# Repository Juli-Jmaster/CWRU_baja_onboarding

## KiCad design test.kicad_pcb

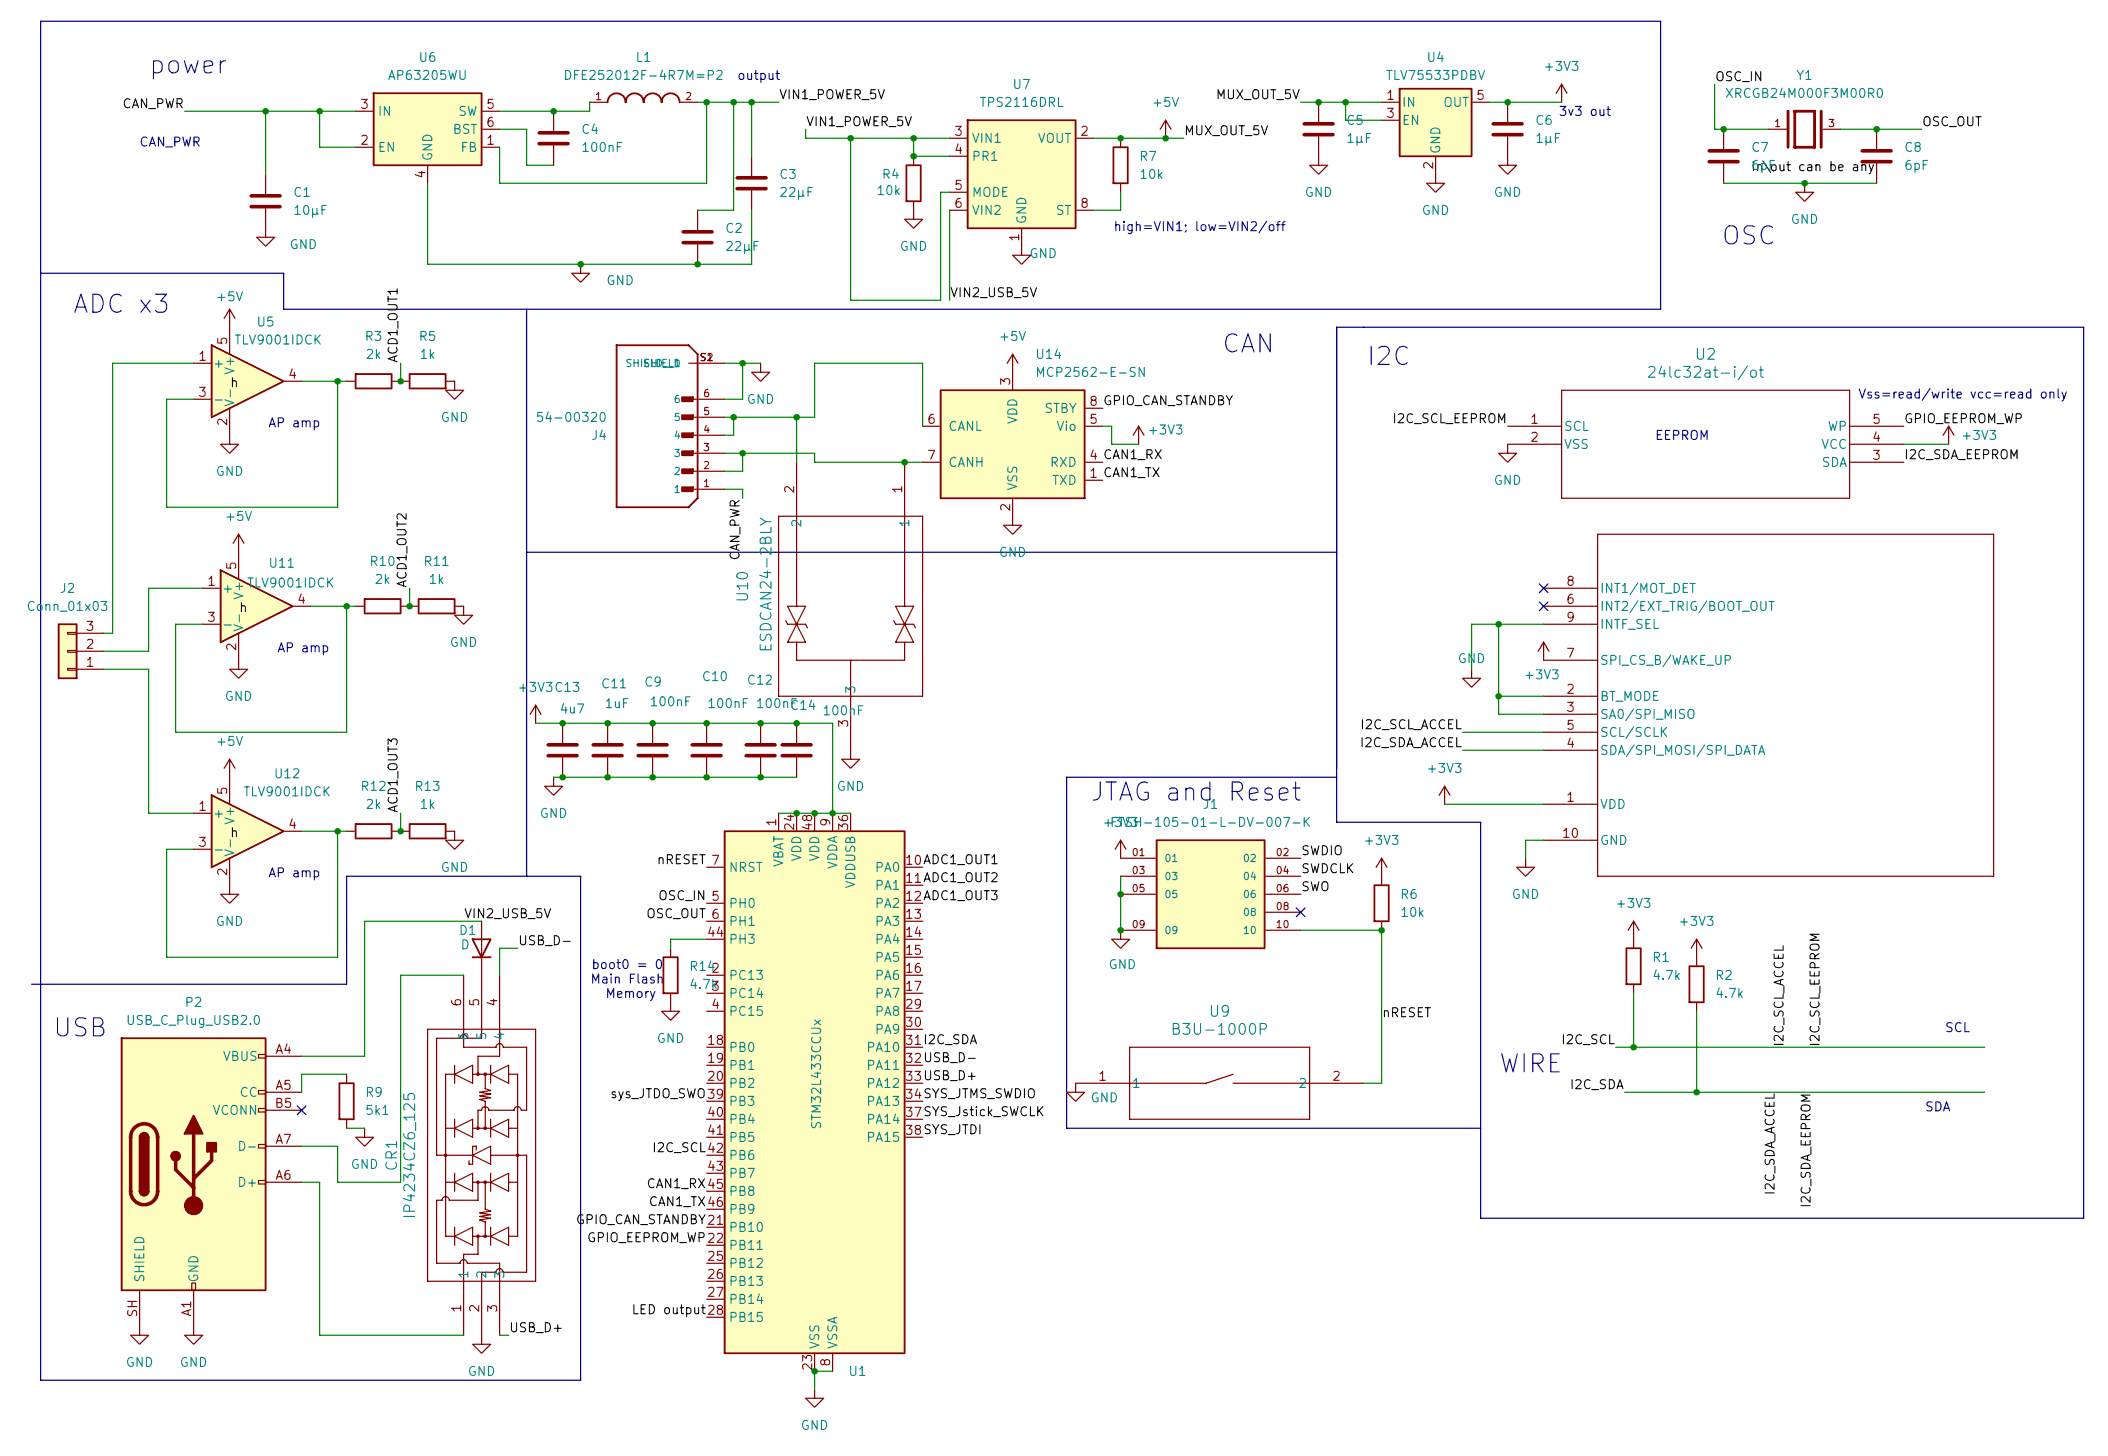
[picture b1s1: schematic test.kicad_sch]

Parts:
C1: 10μF; C_0603_1608Metric_Pad1.08x0.95mm_HandSolder
C2, C3: 22μF; C_0603_1608Metric_Pad1.08x0.95mm_HandSolder
C4, C9, C10, C12, C14: 100nF; C_0603_1608Metric_Pad1.08x0.95mm_HandSolder
C5, C6: 1μF; C_0603_1608Metric_Pad1.08x0.95mm_HandSolder
C7, C8: 6pF; C_0603_1608Metric_Pad1.08x0.95mm_HandSolder
C11: 1uF; C_0603_1608Metric_Pad1.08x0.95mm_HandSolder
C13: 4u7; C_0603_1608Metric_Pad1.08x0.95mm_HandSolder
CR1: IP4234CZ6_125; TSOP6_SOT457_NEX
D1: D; D_MELF
J1: FTSH-105-01-L-DV-007-K; SAMTEC_FTSH-105-01-L-DV-007-K; PARTREV H
J2: Conn_01x03; Tag-Connect_TC2030-IDC-NL_2x03_P1.27mm_Vertical
J4: 54-00320; TENSILITY_54-00320; PARTREV A
L1: DFE252012F-4R7M=P2; INDC2520X120N
P2: USB_C_Plug_USB2.0; USB_C_Receptacle_GCT_USB4085
R1, R2, R14: 4.7k; R_0603_1608Metric_Pad0.98x0.95mm_HandSolder
R3, R10, R12: 2k; R_0603_1608Metric_Pad0.98x0.95mm_HandSolder
R4, R6, R7: 10k; R_0603_1608Metric_Pad0.98x0.95mm_HandSolder
R5, R11, R13: 1k; R_0603_1608Metric_Pad0.98x0.95mm_HandSolder
R9: 5k1; R_0603_1608Metric_Pad0.98x0.95mm_HandSolder
U1: STM32L433CCUx; QFN-48-1EP_7x7mm_P0.5mm_EP5.6x5.6mm
U2: 24lc32at-i/ot; SOT-24-5_MC_MCH
U3: FXLS8974CFR3; DFN10_2X2_STM
U4: TLV75533PDBV; SOT-23-5
U5, U11, U12: TLV9001IDCK; SOT-353_SC-70-5
U6: AP63205WU; TSOT-23-6
U7: TPS2116DRL; SOT-583-8
U9: B3U-1000P
U10: ESDCAN24-2BLY; SOT_24-2BLY_STM
U14: MCP2562-E-SN; SOIC-8_3.9x4.9mm_P1.27mm
Y1: XRCGB24M000F3M00R0; OSC_XRCGB24M000F3M00R0; PARTREV N/A

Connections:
/ACD1_OUT1: R3.1, R5.1
/ACD1_OUT2: R10.1, R11.1
/ACD1_OUT3: R12.1, R13.1
/ADC1_OUT1: U1.10 (PA0)
/ADC1_OUT2: U1.11 (PA1)
/ADC1_OUT3: U1.12 (PA2)
/CAN1_RX: U1.45 (PB8), U14.4 (RXD); also elsewhere on the board
/CAN1_TX: U1.46 (PB9), U14.1 (TXD); also elsewhere on the board
/CAN_PWR: C1.1, J4.1, U6.2 (EN), U6.3 (IN)
/GPIO_CAN_STANDBY: U1.21 (PB10), U14.8 (STBY); also elsewhere on the board
/GPIO_EEPROM_WP: U1.22 (PB11), U2.5 (WP)
/I2C_SCL: R1.2, U1.42 (PB6), U2.1 (SCL), U3.5 (SCL/SCLK)
/I2C_SDA: R2.2, U1.31 (PA10), U2.3 (SDA), U3.4 (SDA/SPI_MOSI/SPI_DATA)
/LED output: U1.28 (PB15)
/OSC_IN: C7.1, U1.5 (PH0), Y1.1
/OSC_OUT: C8.1, U1.6 (PH1), Y1.3
/SWDCLK: J1.04
/SWDIO: J1.02
/SWO: J1.06
/SYS_JTDI: U1.38 (PA15)
/SYS_JTMS_SWDIO: U1.34 (PA13)
/SYS_Jstick_SWCLK: U1.37 (PA14)
/USB_D+: CR1.3, U1.33 (PA12)
/USB_D-: CR1.4, U1.32 (PA11)
/VIN1_POWER_5V: C2.1, C3.1, L1.2, R4.1, U6.1 (FB), U7.3 (VIN1), U7.4 (PR1), U7.5 (MODE)
/VIN2_USB_5V: D1.2 (A), P2.A4 (VBUS), P2.A9 (VBUS), P2.B4 (VBUS), P2.B9 (VBUS), U7.6 (VIN2)
/nRESET: J1.10, R6.2, U1.7 (NRST), U9.2
/sys_JTDO_SWO: U1.39 (PB3)
GND: C1.2, C2.2, C3.2, C5.2, C6.2, C7.2, C8.2, C9.2, C10.2, C11.2, C12.2, C13.2, C14.2, CR1.2, J1.03, J1.05, J1.09, J4.6, J4.S1 (SHIELD), J4.S2 (SHIELD__1), P2.A1 (GND), P2.A12 (GND), P2.B1 (GND), P2.B12 (GND), P2.SH (SHIELD), R4.2, R5.2, R9.2, R11.2, R13.2, R14.2, U1.8 (VSSA), U1.23 (VSS), U1.35 (VSS), U1.47 (VSS), U1.49 (VSS), U2.2 (VSS), U3.2 (BT_MODE), U3.3 (SA0/SPI_MISO), U3.9 (INTF_SEL), U3.10 (GND), U4.2 (GND), U5.2 (V-), U6.4 (GND), U7.1 (GND), U9.1, U10.3, U11.2 (V-), U12.2 (V-), U14.2 (VSS); also elsewhere on the board
unnamed: CR1.5, D1.1 (K)
unnamed: J2.1, U12.1 (+)
unnamed: J2.2, U11.1 (+)
unnamed: J2.3, U5.1 (+)
unnamed: P2.A5 (CC), R9.1
unnamed: CR1.1, P2.A6 (D+)
unnamed: CR1.6, P2.A7 (D-)
unnamed: R14.1, U1.44 (PH3)
unnamed: R3.2, U5.3 (-), U5.4
unnamed: C4.2, U6.6 (BST)
unnamed: C4.1, L1.1, U6.5 (SW)
unnamed: R7.2, U7.8 (ST)
unnamed 41: J4.2, J4.3, U10.1, U14.7 (CANH); also elsewhere on the board
unnamed 42: J4.4, J4.5, U10.2, U14.6 (CANL); also elsewhere on the board
unnamed: R10.2, U11.3 (-), U11.4
unnamed: R12.2, U12.3 (-), U12.4

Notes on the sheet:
3v3 out
AP amp
WIRE
power
SDA
ADC x3
OSC
boot0 = 0 Main Flash Memory
Vss=read/write vcc=read only
JTAG and Reset
high=VIN1; low=VIN2/off
EEPROM
USB
output
CAN_PWR
SCL
I2C
CAN

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
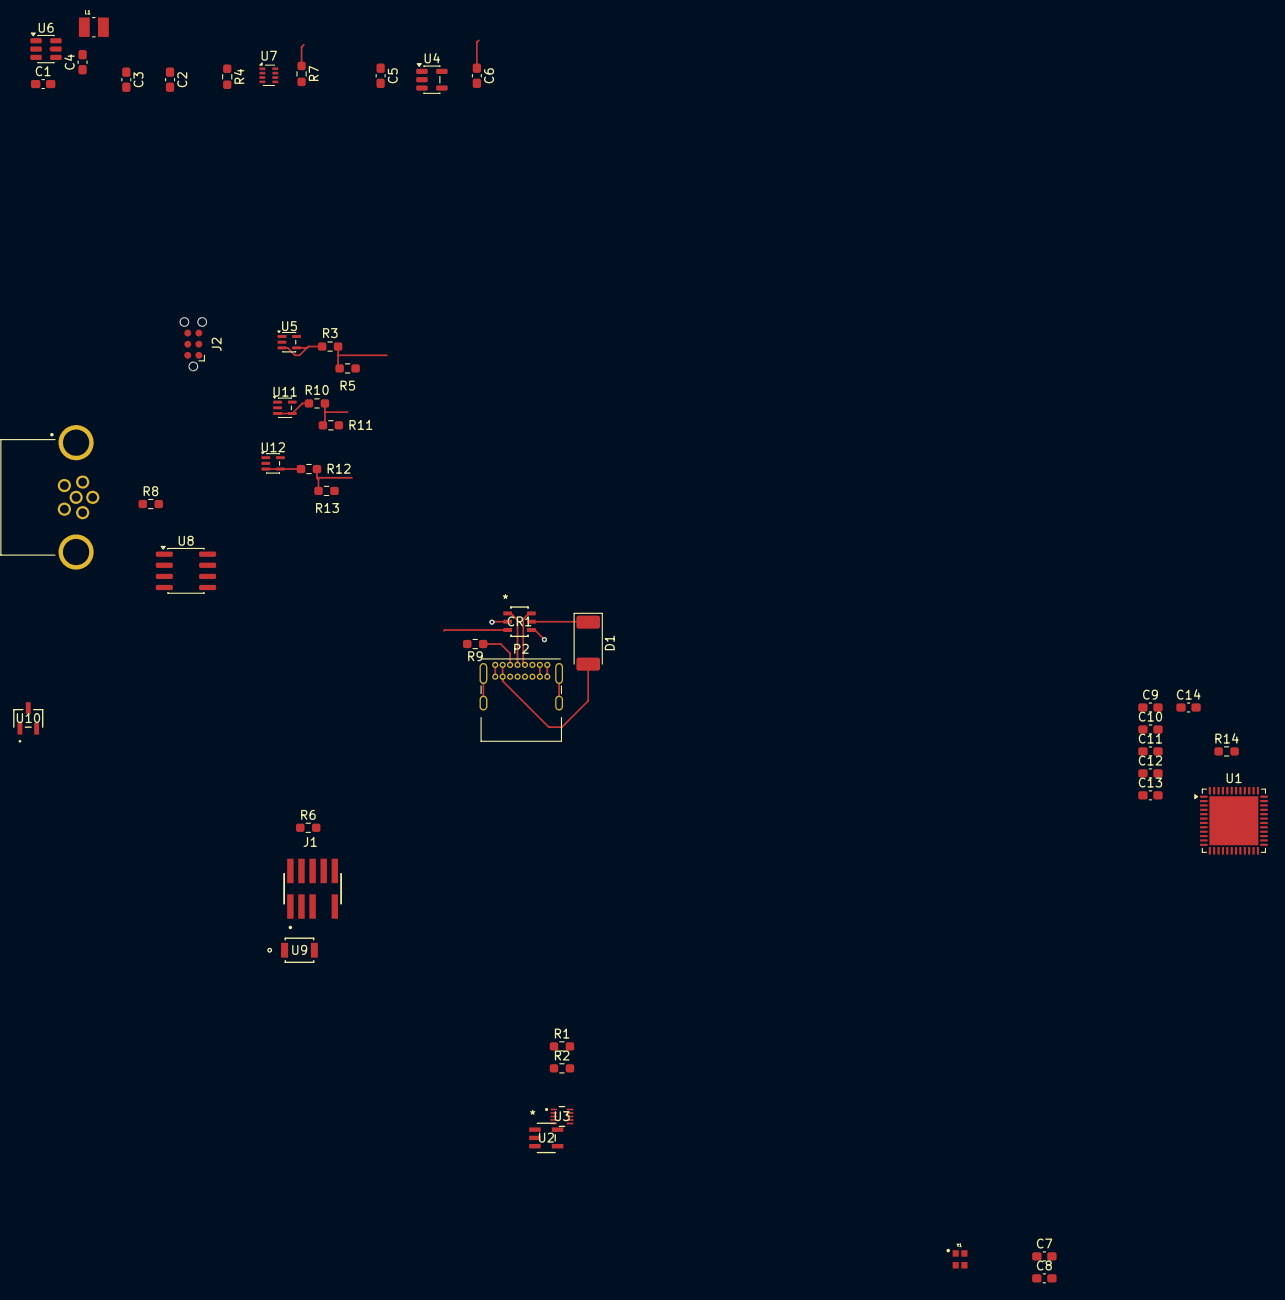
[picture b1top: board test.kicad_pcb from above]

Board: 4 copper layers, 48 parts (0 on the bottom side), 37 nets.

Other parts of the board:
R8: 10k; R_0603_1608Metric_Pad0.98x0.95mm_HandSolder
U8: MCP2561-E-SN; SOIC-8_3.9x4.9mm_P1.27mm

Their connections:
/CAN1_RX: U8.4 (RXD); also elsewhere on the board
/CAN1_TX: U8.1 (TXD); also elsewhere on the board
/GPIO_CAN_STANDBY: U8.8 (STBY); also elsewhere on the board
GND: R8.2, U8.2 (VSS); also elsewhere on the board
unnamed 41: U8.7 (CANH); also elsewhere on the board
unnamed 42: U8.6 (CANL); also elsewhere on the board
unnamed: R8.1, U8.5 (SPLIT)

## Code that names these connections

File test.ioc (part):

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Mcu.Name=STM32L433C(B-C)Tx
Mcu.Package=LQFP48
Mcu.UserName=STM32L433CCTx
PA0.Signal=ADCx_IN5
PA1.Signal=ADCx_IN6
PA10.Mode=I2C
PA10.Signal=I2C1_SDA
PA11.GPIOParameters=GPIO_Label
PA11.GPIO_Label=USB_D-
PA11.Mode=Device
PA11.Signal=USB_DM
PA12.GPIOParameters=GPIO_Label
PA12.GPIO_Label=USB_D+
PA12.Mode=Device
PA12.Signal=USB_DP
PA13\ (JTMS-SWDIO).Mode=JTAG_4_pins
PA13\ (JTMS-SWDIO).Signal=SYS_JTMS-SWDIO
PA14\ (JTCK-SWCLK).Mode=JTAG_4_pins
PA14\ (JTCK-SWCLK).Signal=SYS_JTCK-SWCLK
PA15\ (JTDI).Mode=JTAG_4_pins
PA15\ (JTDI).Signal=SYS_JTDI
PA2.Signal=ADCx_IN7
PA8.GPIOParameters=GPIO_Label
PA8.GPIO_Label=GPIO OP amp in
PA8.Signal=GPIO_Input
PB10.GPIOParameters=GPIO_Label
PB10.GPIO_Label=GPIO_CAN_STANDBY
PB10.Signal=GPIO_Input
PB11.GPIOParameters=GPIO_Label
PB11.GPIO_Label=GPIO_EEPROM_WP
PB11.Signal=GPIO_Output
PB15.GPIOParameters=GPIO_Label
PB15.GPIO_Label=GPIO ouput LED
PB15.Signal=GPIO_Output
PB3\ (JTDO-TRACESWO).Mode=JTAG_4_pins
PB3\ (JTDO-TRACESWO).Signal=SYS_JTDO-SWO
PB6.Mode=I2C
PB6.Signal=I2C1_SCL
PB8.Mode=CAN_Activate
PB8.Signal=CAN1_RX
PB9.Mode=CAN_Activate
PB9.Signal=CAN1_TX
PH0-OSC_IN\ (PH0).Mode=HSE-External-Oscillator
PH0-OSC_IN\ (PH0).Signal=RCC_OSC_IN
PH1-OSC_OUT\ (PH1).Mode=HSE-External-Oscillator
PH1-OSC_OUT\ (PH1).Signal=RCC_OSC_OUT
RCC.HSE_VALUE=8000000
RCC.SYSCLKFreq_VALUE=80000000
RCC.SYSCLKSource=RCC_SYSCLKSOURCE_PLLCLK
board=custom
